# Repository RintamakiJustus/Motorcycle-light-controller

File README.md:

# Motorcycle-light-controller
Smart motorcycle light controller to handle blinkers, PWM led dimming, neopixel daytime running lights and unique light effects. Turns hardwired handlebar buttons to flexible programmable multiuse buttons.

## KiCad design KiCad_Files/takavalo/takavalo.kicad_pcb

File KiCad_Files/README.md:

This controller is made on a custom-made, one sided FR4 PCB. KiCad files found here.

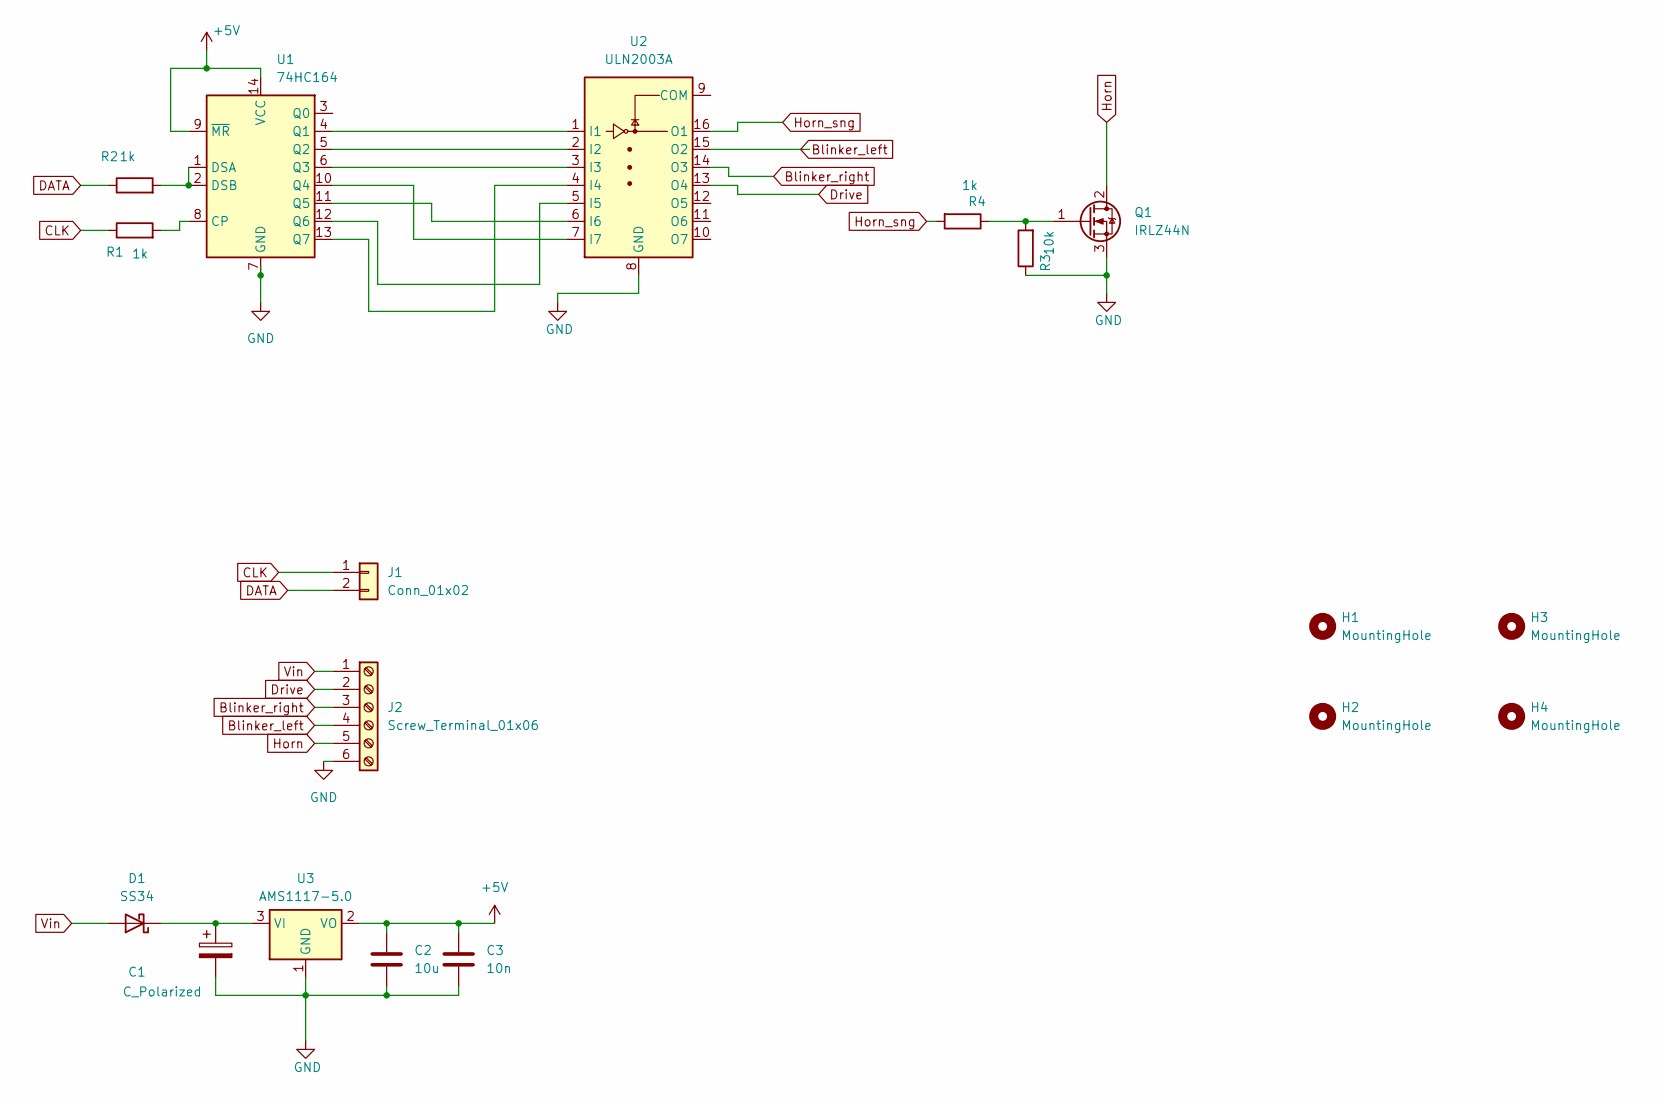
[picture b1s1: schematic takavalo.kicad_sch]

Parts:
C1: C_Polarized; CP_Radial_D6.3mm_P2.50mm
C2: 10u; C_0603_1608Metric
C3: 10n; C_0603_1608Metric
D1: SS34; D_SMP_DO-220AA
H1, H2, H3, H4: MountingHole; MountingHole_3.2mm_M3
J1: Conn_01x02; JST_EH_B2B-EH-A_1x02_P2.50mm_Vertical
J2: Screw_Terminal_01x06; Altech_AK100_1x06_P5.00mm
Q1: IRLZ44N; TO-220-3_Vertical
R1, R2, R4: 1k; R_1206_3216Metric_Pad1.30x1.75mm_HandSolder
R3: 10k; R_1206_3216Metric_Pad1.30x1.75mm_HandSolder
U1: 74HC164; DIP-14_W7.62mm
U2: ULN2003A; SOIC-16_3.9x9.9mm_P1.27mm
U3: AMS1117-5.0; SOT-223-3_TabPin2

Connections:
+5V: C2.1, C3.1, U1.9 (~MR), U1.14 (VCC), U3.2 (VO)
Blinker_left: J2.4, U2.15 (O2)
Blinker_right: J2.3, U2.14 (O3)
CLK: J1.1, R1.1
DATA: J1.2, R2.1
Drive: J2.2, U2.13 (O4)
GND: C1.2, C2.2, C3.2, J2.6, Q1.3 (S), R3.1, U1.7 (GND), U2.8 (GND), U3.1 (GND)
Horn: J2.5, Q1.2 (D)
Horn_sng: R4.2, U2.16 (O1)
unnamed: C1.1, D1.1 (K), U3.3 (VI)
unnamed: Q1.1 (G), R3.2, R4.1
unnamed: R1.2, U1.8 (CP)
unnamed: R2.2, U1.1 (DSA), U1.2 (DSB)
unnamed: U1.4 (Q1), U2.1 (I1)
unnamed: U1.5 (Q2), U2.2 (I2)
unnamed: U1.6 (Q3), U2.3 (I3)
unnamed: U1.10 (Q4), U2.7 (I7)
unnamed: U1.11 (Q5), U2.6 (I6)
unnamed: U1.12 (Q6), U2.5 (I5)
unnamed: U1.13 (Q7), U2.4 (I4)
Vin: D1.2 (A), J2.1

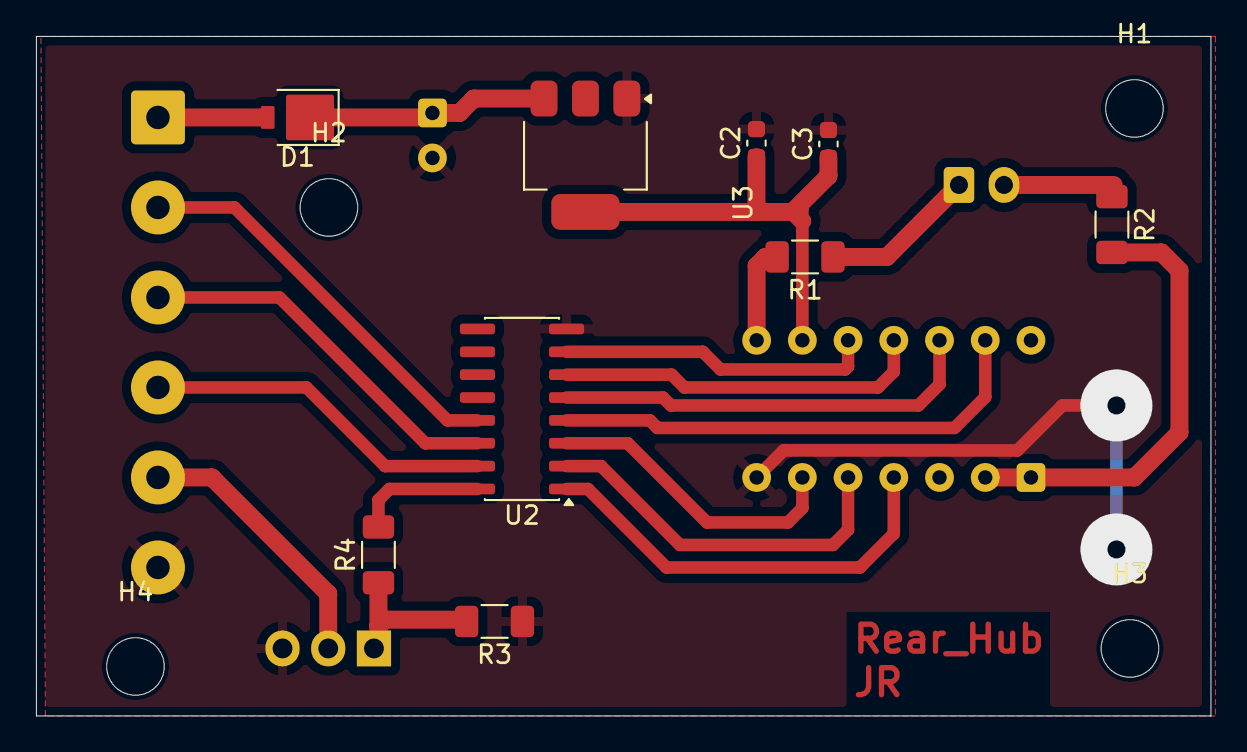
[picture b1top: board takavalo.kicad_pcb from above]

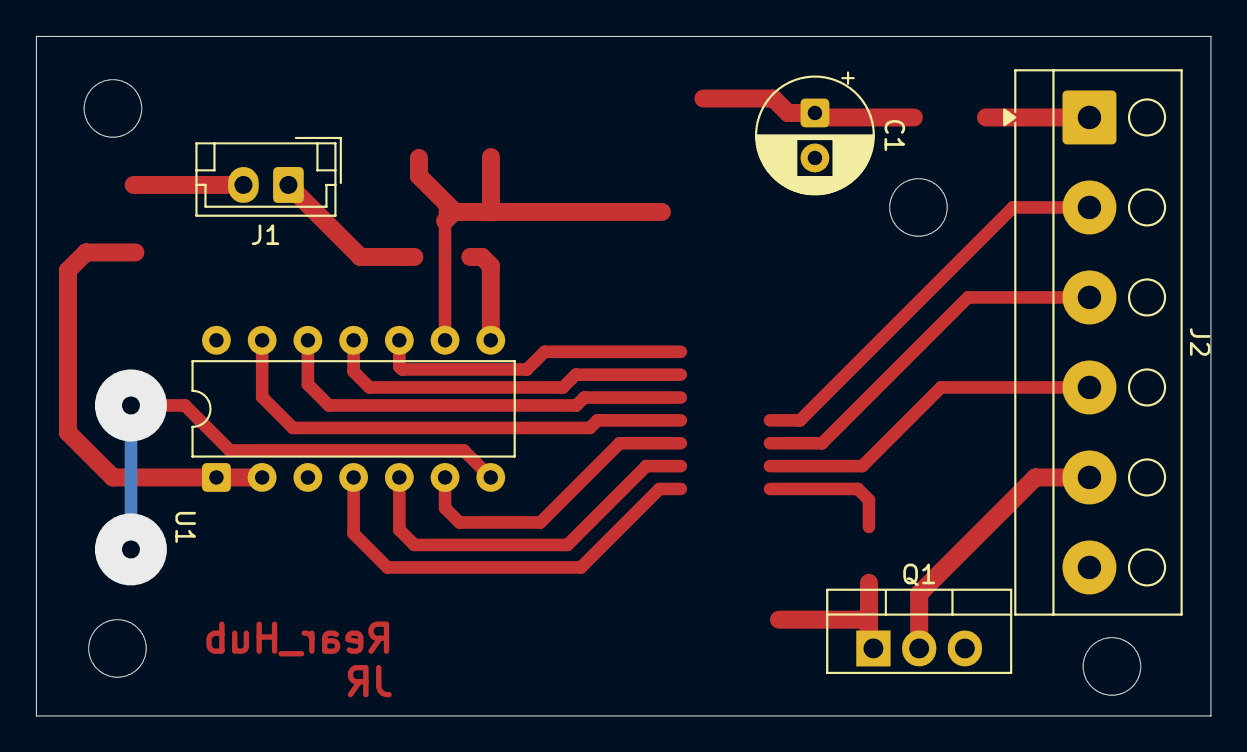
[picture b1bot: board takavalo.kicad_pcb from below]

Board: 2 copper layers, 65.2 x 37.8 mm, 18 parts (5 on the bottom side), 21 nets.

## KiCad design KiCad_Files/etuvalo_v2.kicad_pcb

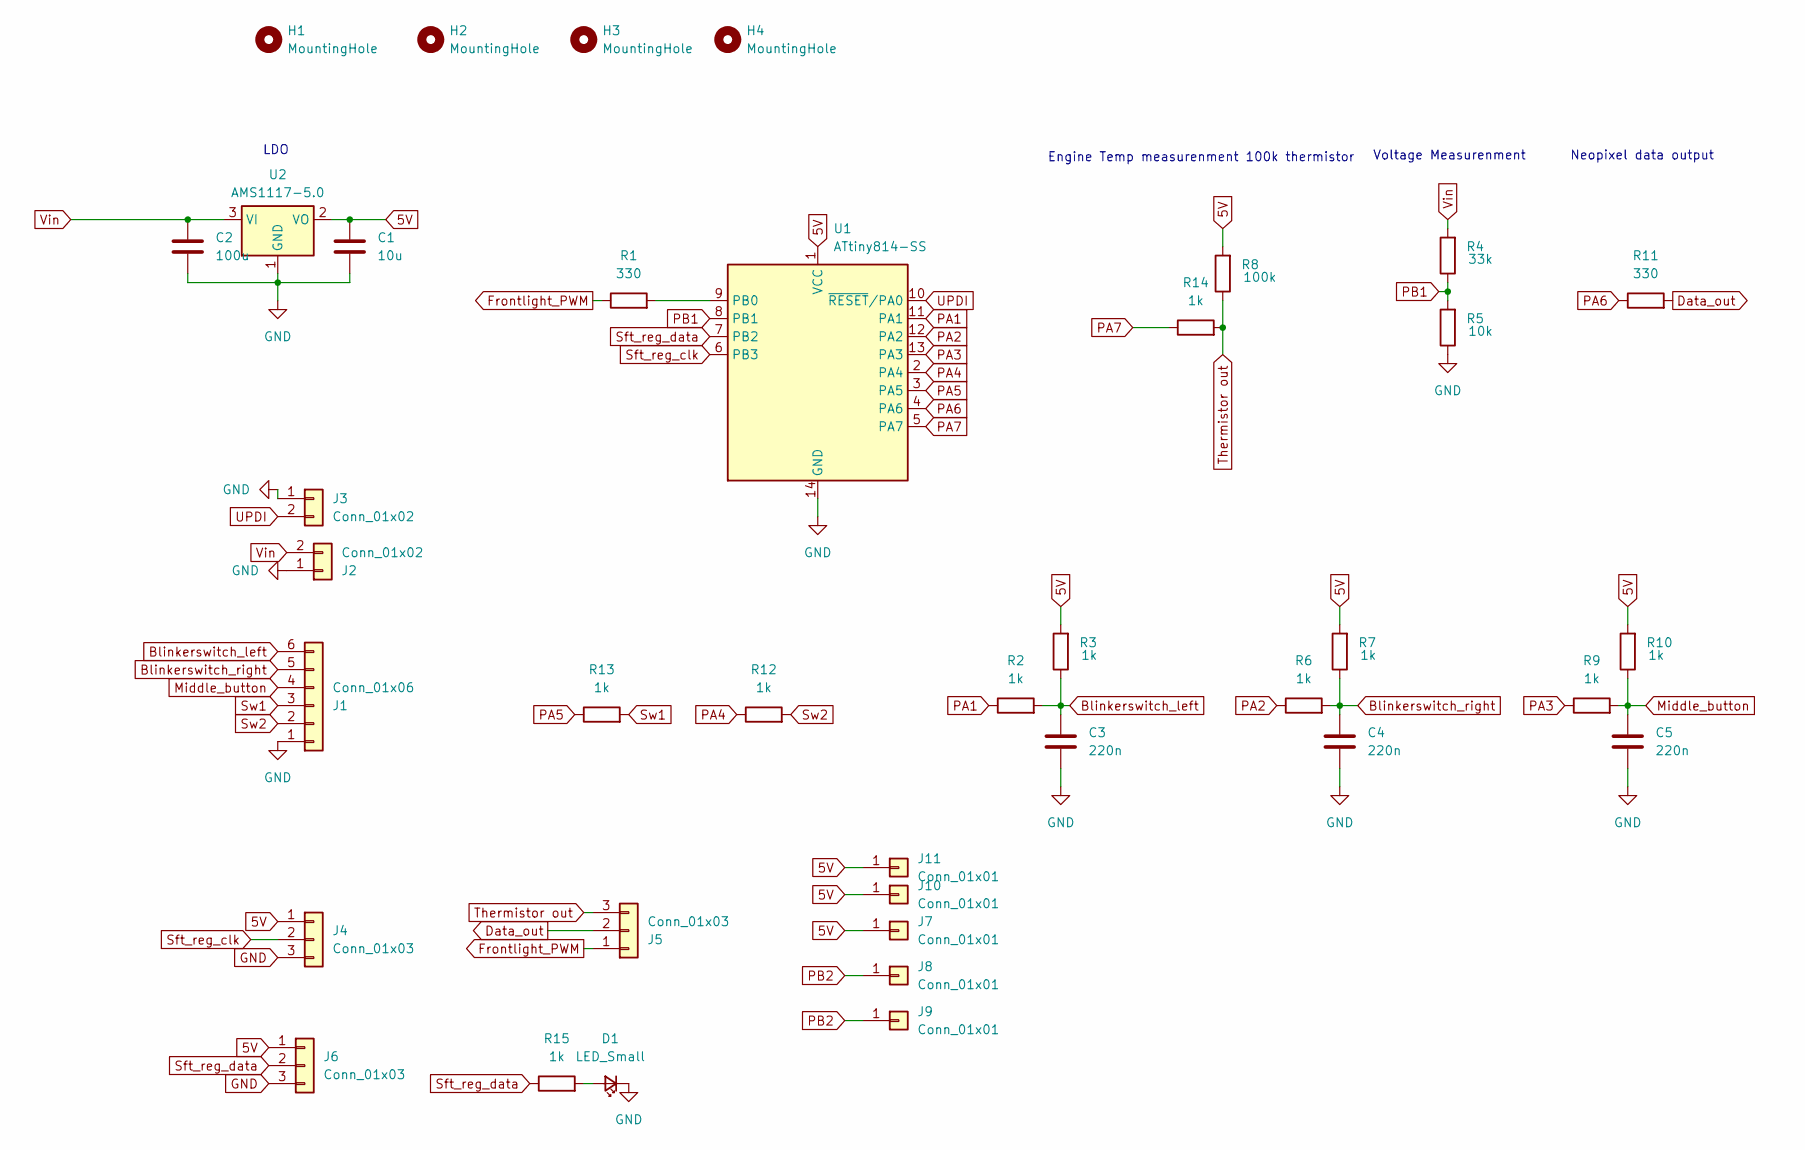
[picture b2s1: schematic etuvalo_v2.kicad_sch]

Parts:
C1: 10u; C_0603_1608Metric_Pad1.08x0.95mm_HandSolder
C2: 100u; C_0603_1608Metric_Pad1.08x0.95mm_HandSolder
C3, C4, C5: 220n; C_0603_1608Metric_Pad1.08x0.95mm_HandSolder
D1: LED_Small; C_0603_1608Metric_Pad1.08x0.95mm_HandSolder
H1, H2, H3, H4: MountingHole; TestPoint_THTPad_D4.0mm_Drill2.0mm
J1: Conn_01x06; JST_EH_B6B-EH-A_1x06_P2.50mm_Vertical
J2, J3: Conn_01x02; JST_EH_B2B-EH-A_1x02_P2.50mm_Vertical
J4, J5, J6: Conn_01x03; JST_EH_B3B-EH-A_1x03_P2.50mm_Vertical
J7, J8, J9, J10, J11: Conn_01x01; PinSocket_1x01_P1.27mm_Vertical
R1, R11: 330; R_1206_3216Metric_Pad1.30x1.75mm_HandSolder
R2, R3, R6, R7, R9, R10, R12, R13, R14, R15: 1k; R_1206_3216Metric_Pad1.30x1.75mm_HandSolder
R4: 33k; R_1206_3216Metric_Pad1.30x1.75mm_HandSolder
R5: 10k; R_1206_3216Metric_Pad1.30x1.75mm_HandSolder
R8: 100k; R_1206_3216Metric_Pad1.30x1.75mm_HandSolder
U1: ATtiny814-SS; SOIC-14_3.9x8.7mm_P1.27mm
U2: AMS1117-5.0; SOT-223-3_TabPin2

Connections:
5V: C1.1, J4.1, J6.1, J7.1, J10.1, J11.1, R3.2, R7.2, R8.2, R10.2, U1.1 (VCC), U2.2 (VO)
Blinkerswitch_left: C3.1, J1.6, R2.2, R3.1
Blinkerswitch_right: C4.1, J1.5, R6.2, R7.1
Data_out: J5.2, R11.2
Frontlight_PWM: J5.1, R1.1
GND: C1.2, C2.2, C3.2, C4.2, C5.2, D1.1 (K), J1.1, J2.1, J3.1, J4.3, J6.3, R5.1, U1.14 (GND), U2.1 (GND)
Middle_button: C5.1, J1.4, R9.2, R10.1
unnamed: D1.2 (A), R15.2
unnamed: R1.2, U1.9 (PB0)
PA1: R2.1, U1.11 (PA1)
PA2: R6.1, U1.12 (PA2)
PA3: R9.1, U1.13 (PA3)
PA4: R12.1, U1.2 (PA4)
PA5: R13.1, U1.3 (PA5)
PA6: R11.1, U1.4 (PA6)
PA7: R14.1, U1.5 (PA7)
PB1: R4.1, R5.2, U1.8 (PB1)
Sft_reg_clk: J4.2, U1.6 (PB3)
Sw1: J1.3, R13.2
Sw2: J1.2, R12.2
Thermistor out: J5.3, R8.1, R14.2
UPDI: J3.2, U1.10 (~RESET/PA0)
Vin: C2.1, J2.2, R4.2, U2.3 (VI)

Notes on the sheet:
Voltage Measurenment
LDO
Neopixel data output
Engine Temp measurenment 100k thermistor

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
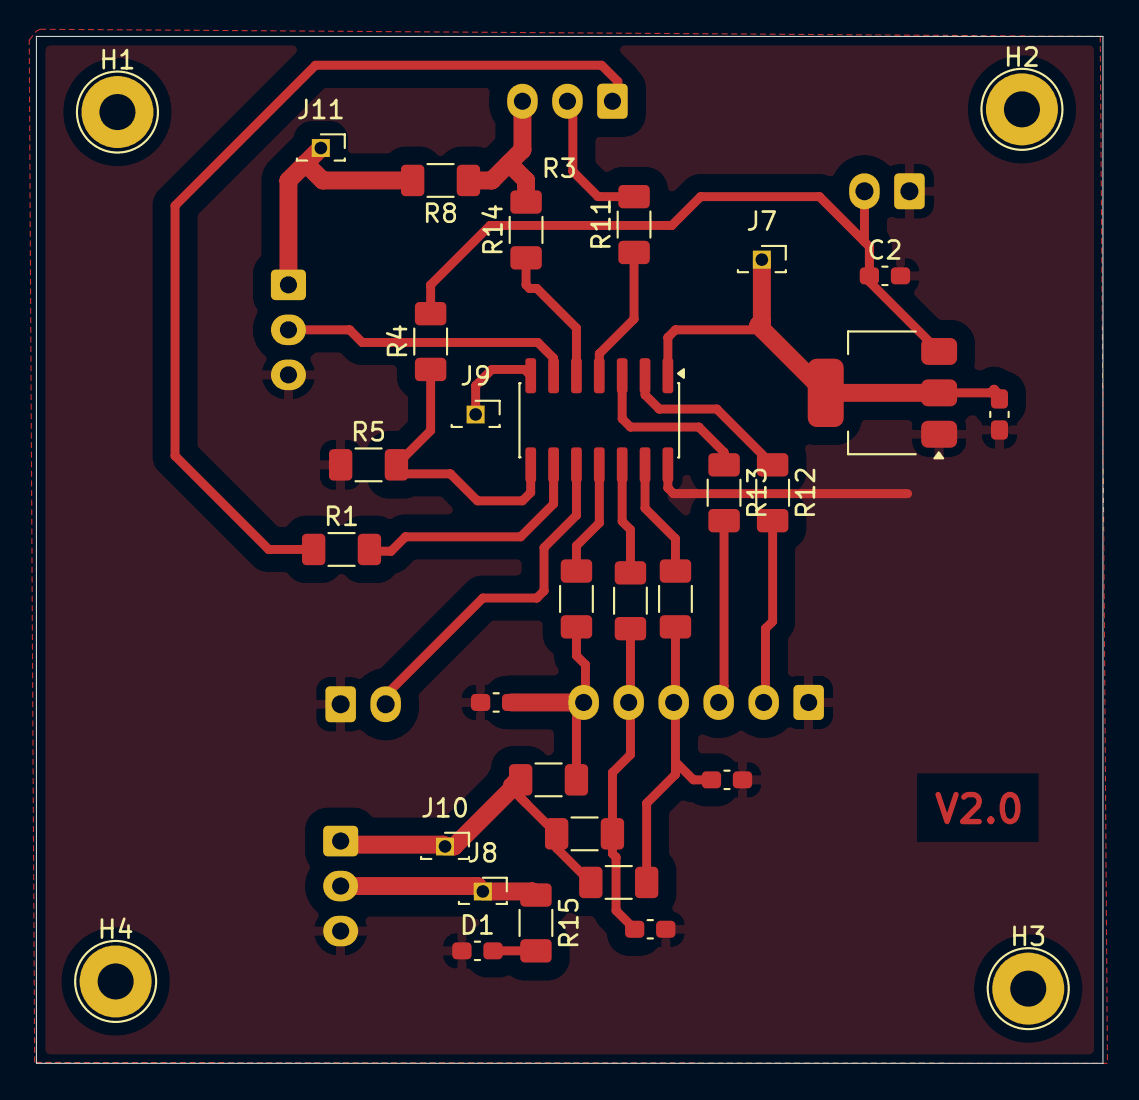
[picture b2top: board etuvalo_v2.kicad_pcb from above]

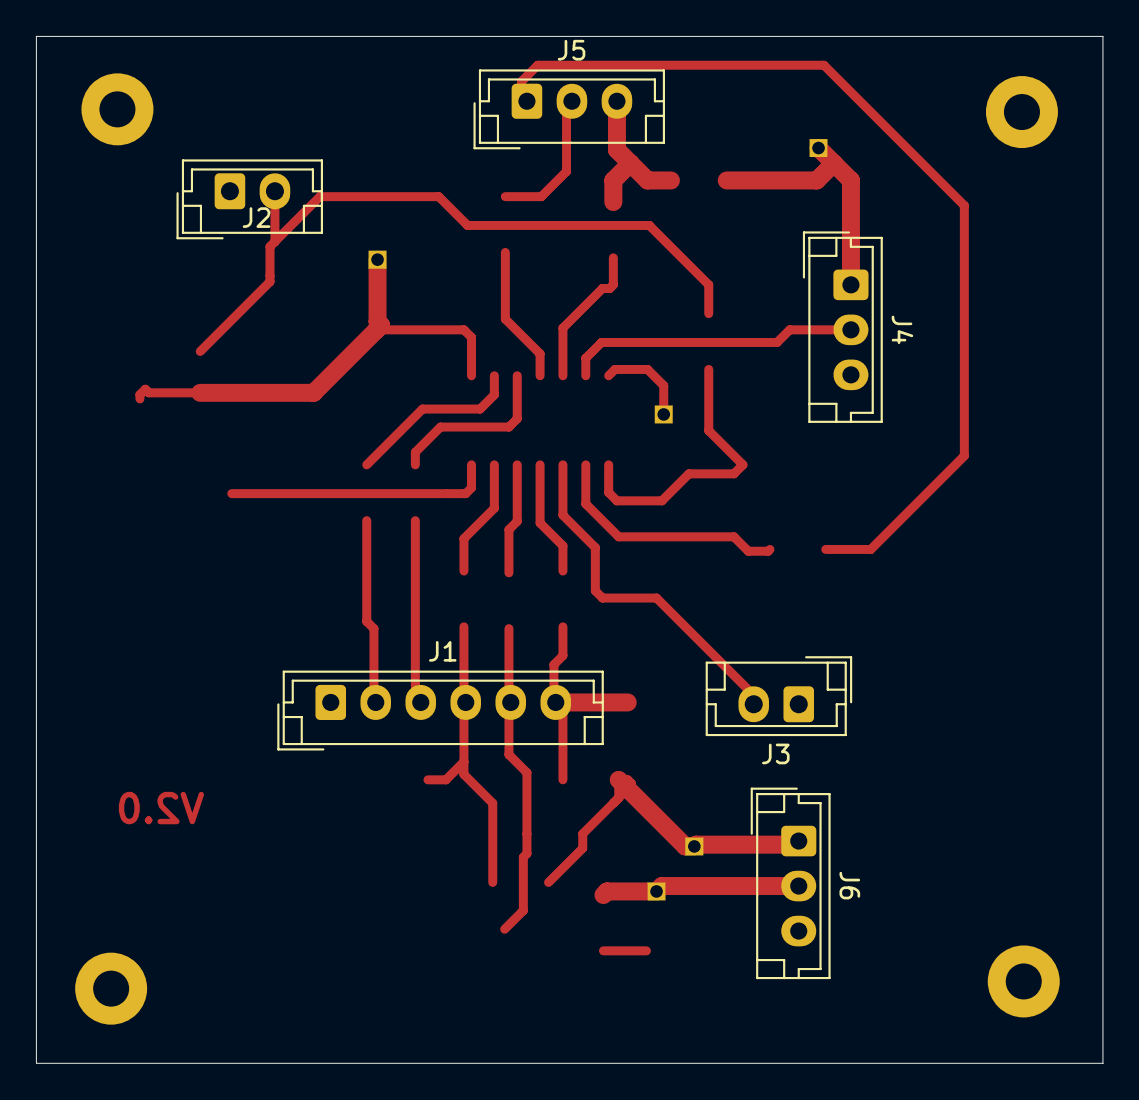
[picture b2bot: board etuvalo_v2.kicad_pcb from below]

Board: 2 copper layers, 59.2 x 57.0 mm, 38 parts (6 on the bottom side), 24 nets.

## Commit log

2026-01-05 Added software and KiCad files
2026-05-07 "C:\Users\Public\Desktop\Zotero.lnk"
2026-05-09 etch mask
